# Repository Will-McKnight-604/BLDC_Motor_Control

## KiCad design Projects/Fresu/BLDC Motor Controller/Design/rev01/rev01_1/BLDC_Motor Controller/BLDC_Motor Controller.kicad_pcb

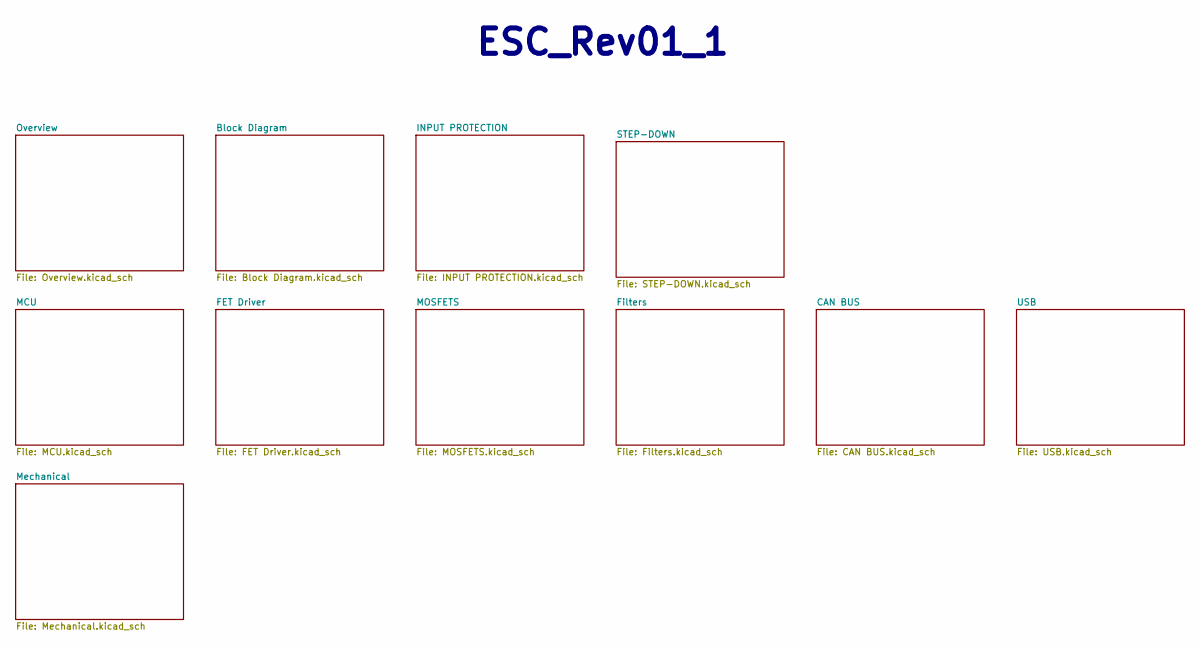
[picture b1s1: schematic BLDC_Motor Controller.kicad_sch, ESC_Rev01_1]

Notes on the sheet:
${TITLE}

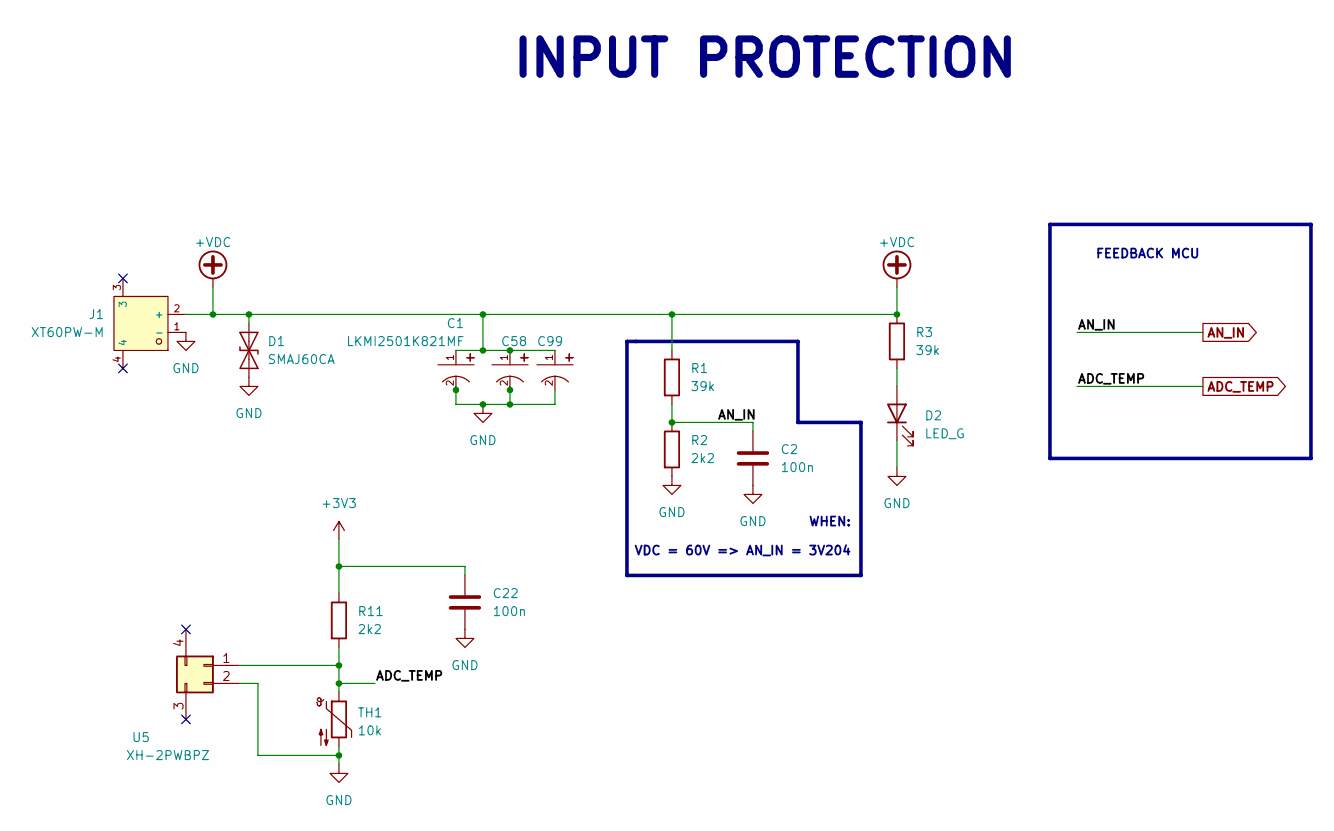
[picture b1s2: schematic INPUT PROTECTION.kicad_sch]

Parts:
C1, C58, C99: LKMI2501K821MF; CAP-TH_BD18.0-P7.50-D1.2-SIDE; LCSC C443097
C2, C22: 100n; C_0603_1608Metric
D1: SMAJ60CA; D_SMA
D2: LED_G; LED_1206_3216Metric
J1: XT60PW-M; CONN-TH_XT60PW-M; LCSC C98732
R1, R3: 39k; R_0603_1608Metric_Pad0.98x0.95mm_HandSolder
R2, R11: 2k2; R_0603_1608Metric_Pad0.98x0.95mm_HandSolder
TH1: 10k; R_0603_1608Metric_Pad0.98x0.95mm_HandSolder
U5: XH-2PWBPZ; CONN-SMD_XH-2PWBPZ

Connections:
+3V3: C22.1, R11.1; also elsewhere on the board
+VDC: C1.1, C58.1, C99.1, D1.2 (A2), J1.2 (+), R1.1, R3.1; also elsewhere on the board
ADC_TEMP: R11.2, TH1.1, U5.1; also elsewhere on the board
AN_IN: C2.1, R1.2, R2.1; also elsewhere on the board
GND: C1.2, C2.2, C22.2, C58.2, C99.2, D1.1 (A1), D2.1 (K), J1.1 (-), R2.2, TH1.2, U5.2; also elsewhere on the board
unnamed: D2.2 (A), R3.2

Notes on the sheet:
INPUT PROTECTION
FEEDBACK MCU
WHEN: VDC = 60V => AN_IN = 3V204

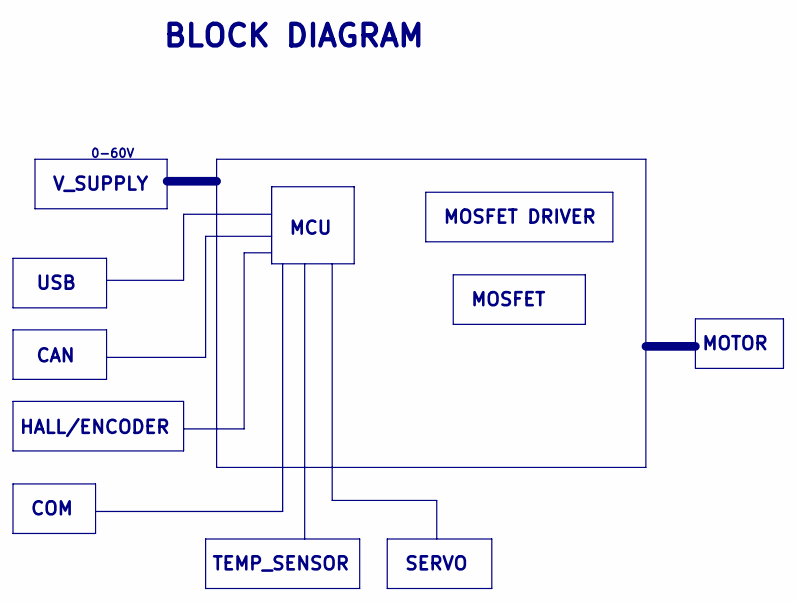
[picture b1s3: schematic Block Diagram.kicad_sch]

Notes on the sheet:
MCU
MOSFET
V_SUPPLY
MOTOR
TEMP_SENSOR
BLOCK DIAGRAM
USB
HALL/ENCODER
SERVO
COM
0-60V
MOSFET DRIVER
CAN

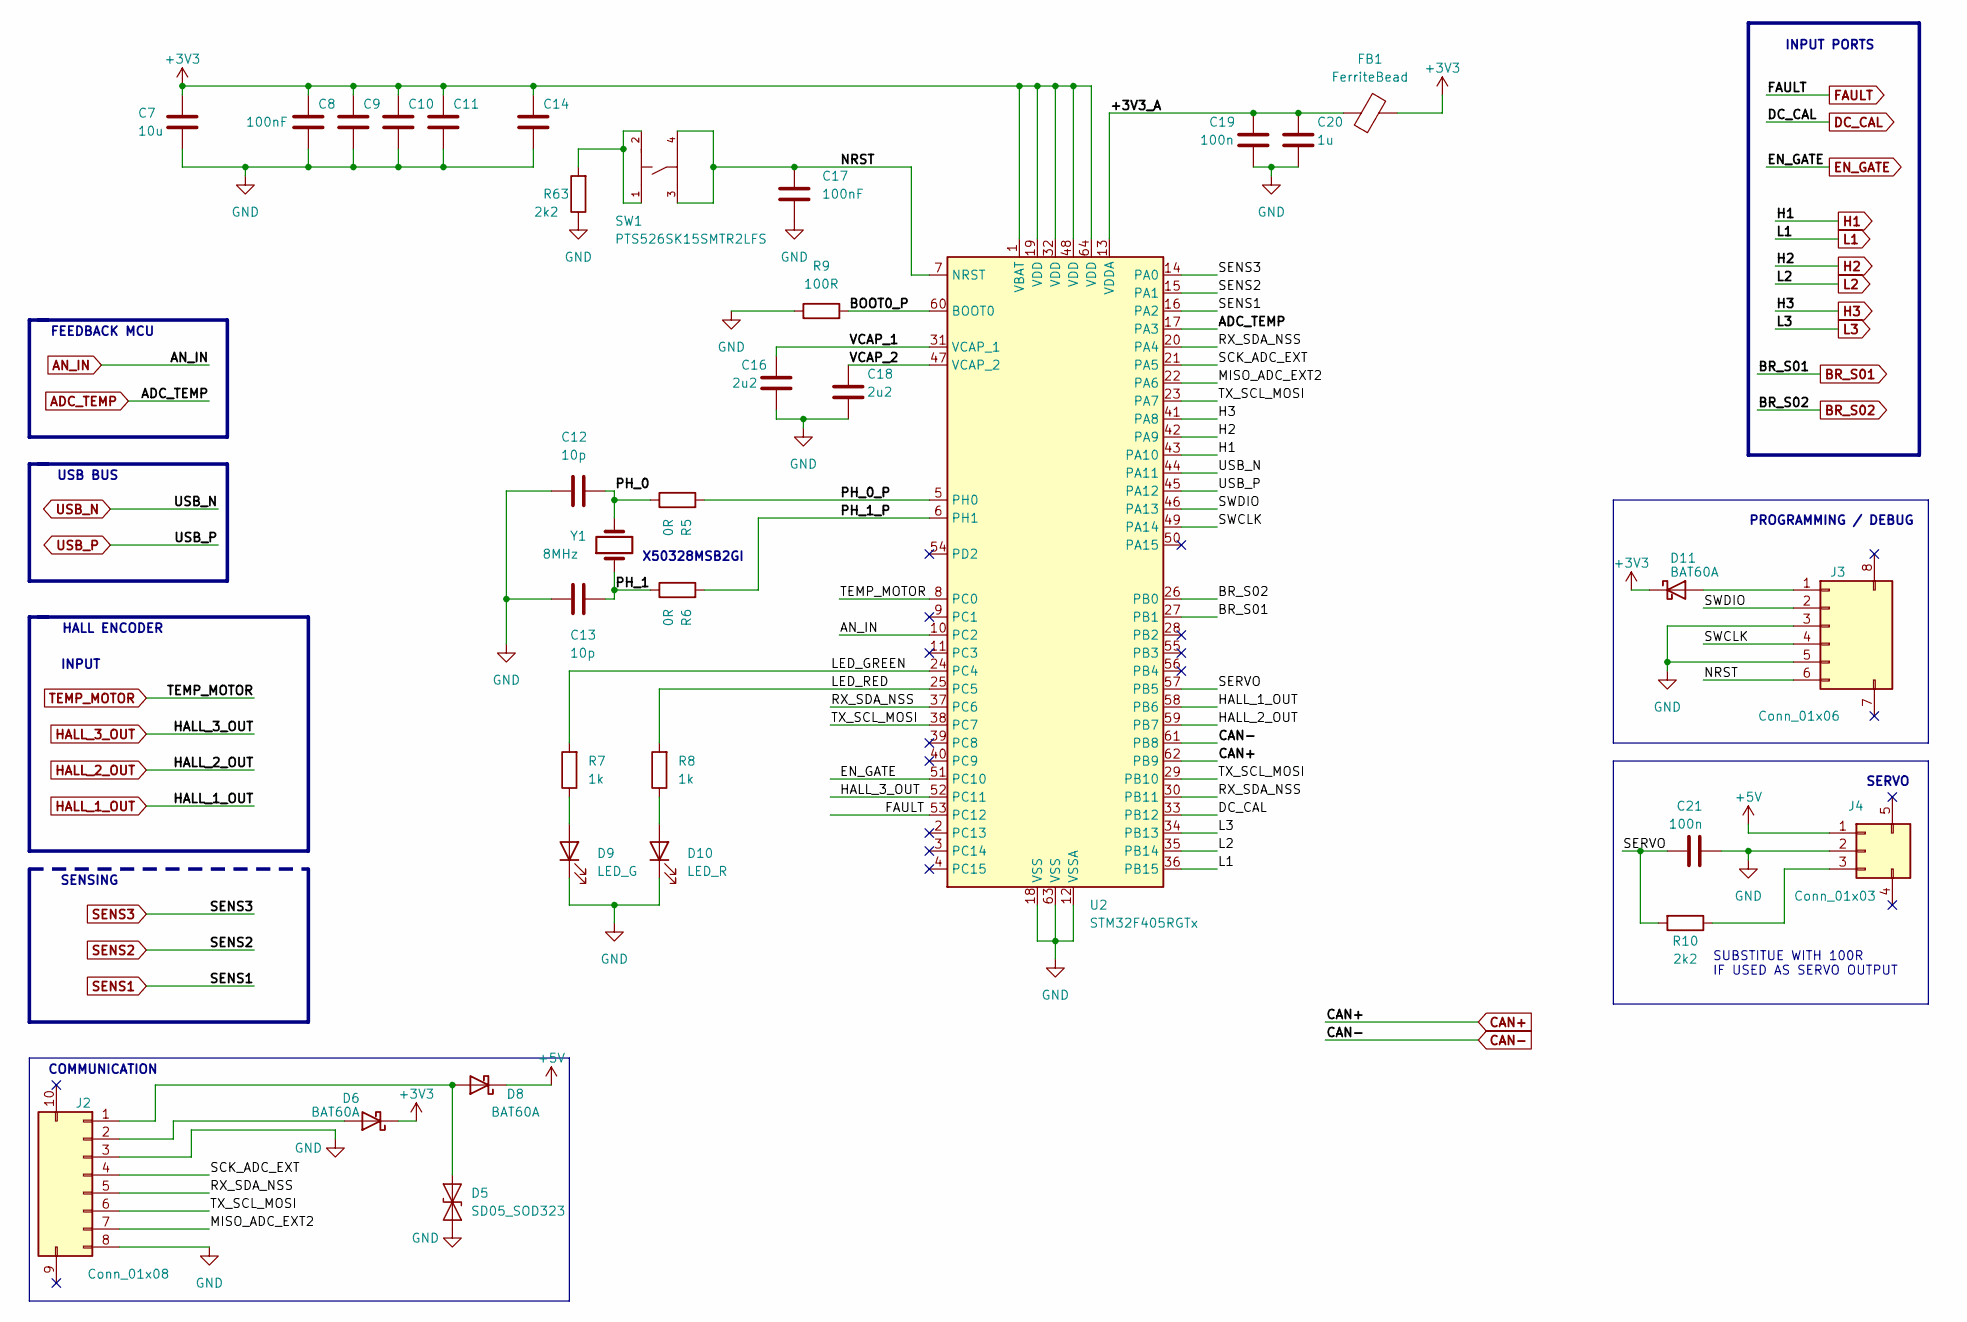
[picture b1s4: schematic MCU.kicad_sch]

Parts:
C7: 10u; C_0603_1608Metric
C8, C9, C10, C11, C14, C17: 100nF; C_0603_1608Metric
C12, C13: 10p; C_0603_1608Metric
C16, C18: 2u2; C_0603_1608Metric
C19, C21: 100n; C_0603_1608Metric
C20: 1u; C_0603_1608Metric
D5: SD05_SOD323; D_SOD-323
D6, D8, D11: BAT60A; D_SOD-323
D9: LED_G; LED_1206_3216Metric
D10: LED_R; LED_1206_3216Metric
FB1: FerriteBead; L_0603_1608Metric_Pad1.05x0.95mm_HandSolder
J2: Conn_01x08; CONN-SMD_8P-P2.50_HX25003-8AWB
J3: Conn_01x06; CONN-SMD_S6B-XH-SM4-TB-LF-SN
J4: Conn_01x03; CONN-SMD_XH-3AWB
R5, R6: 0R; R_0603_1608Metric_Pad0.98x0.95mm_HandSolder
R7, R8: 1k; R_0603_1608Metric_Pad0.98x0.95mm_HandSolder
R9: 100R; R_0603_1608Metric_Pad0.98x0.95mm_HandSolder
R10, R63: 2k2; R_0603_1608Metric_Pad0.98x0.95mm_HandSolder
SW1: PTS526SK15SMTR2LFS; SW-SMD_4P-L5.2-W5.2-P3.70-LS6.4; LCSC C2689521
U2: STM32F405RGTx; LQFP-64_10x10mm_P0.5mm
Y1: 8MHz; CRYSTAL-SMD_L5.0-W3.2

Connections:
+3V3: C7.1, C8.1, C9.1, C10.1, C11.1, C14.1, D6.1 (K), D11.1 (K), FB1.2, U2.1 (VBAT), U2.19 (VDD), U2.32 (VDD), U2.48 (VDD), U2.64 (VDD); also elsewhere on the board
+5V: D8.1 (K), J4.1; also elsewhere on the board
/MCU/+3V3_A: C19.1, C20.1, FB1.1, U2.13 (VDDA)
/MCU/BOOT0_P: R9.2, U2.60 (BOOT0)
/MCU/LED_GREEN: R7.2, U2.24 (PC4)
/MCU/LED_RED: R8.2, U2.25 (PC5)
/MCU/MISO_ADC_EXT2: J2.7, U2.22 (PA6)
/MCU/NRST: C17.1, J3.6, SW1.3, SW1.4, U2.7 (NRST)
/MCU/PH_0: C12.1, R5.1, Y1.2
/MCU/PH_0_P: R5.2, U2.5 (PH0)
/MCU/PH_1: C13.1, R6.1, Y1.1
/MCU/PH_1_P: R6.2, U2.6 (PH1)
/MCU/RX_SDA_NSS: J2.5, U2.20 (PA4), U2.30 (PB11), U2.37 (PC6)
/MCU/SCK_ADC_EXT: J2.4, U2.21 (PA5)
/MCU/SERVO: C21.1, R10.2, U2.57 (PB5)
/MCU/SWCLK: J3.4, U2.49 (PA14)
/MCU/SWDIO: J3.2, U2.46 (PA13)
/MCU/TX_SCL_MOSI: J2.6, U2.23 (PA7), U2.29 (PB10), U2.38 (PC7)
/MCU/VCAP_1: C16.1, U2.31 (VCAP_1)
/MCU/VCAP_2: C18.1, U2.47 (VCAP_2)
ADC_TEMP: U2.17 (PA3); also elsewhere on the board
AN_IN: U2.10 (PC2); also elsewhere on the board
BR_S01: U2.27 (PB1); also elsewhere on the board
BR_S02: U2.26 (PB0); also elsewhere on the board
CAN+: U2.62 (PB9); also elsewhere on the board
CAN-: U2.61 (PB8); also elsewhere on the board
DC_CAL: U2.33 (PB12); also elsewhere on the board
EN_GATE: U2.51 (PC10); also elsewhere on the board
FAULT: U2.53 (PC12); also elsewhere on the board
GND: C7.2, C8.2, C9.2, C10.2, C11.2, C12.2, C13.2, C14.2, C16.2, C17.2, C18.2, C19.2, C20.2, C21.2, D5.1 (A1), D9.1 (K), D10.1 (K), J2.3, J2.8, J3.3, J3.5, J4.2, R9.1, R63.1, U2.12 (VSSA), U2.18 (VSS), U2.63 (VSS); also elsewhere on the board
H1: U2.43 (PA10); also elsewhere on the board
H2: U2.42 (PA9); also elsewhere on the board
H3: U2.41 (PA8); also elsewhere on the board
HALL_1_OUT: U2.58 (PB6); also elsewhere on the board
HALL_2_OUT: U2.59 (PB7); also elsewhere on the board
HALL_3_OUT: U2.52 (PC11); also elsewhere on the board
L1: U2.36 (PB15); also elsewhere on the board
L2: U2.35 (PB14); also elsewhere on the board
L3: U2.34 (PB13); also elsewhere on the board
unnamed: D5.2 (A2), D8.2 (A), J2.1
unnamed: D6.2 (A), J2.2
unnamed: D9.2 (A), R7.1
unnamed: D10.2 (A), R8.1
unnamed: D11.2 (A), J3.1
unnamed: J4.3, R10.1
unnamed: R63.2, SW1.1, SW1.2
SENS1: U2.16 (PA2); also elsewhere on the board
SENS2: U2.15 (PA1); also elsewhere on the board
SENS3: U2.14 (PA0); also elsewhere on the board
TEMP_MOTOR: U2.8 (PC0); also elsewhere on the board
USB_N: U2.44 (PA11); also elsewhere on the board
USB_P: U2.45 (PA12); also elsewhere on the board

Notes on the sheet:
SERVO
INPUT PORTS
USB BUS
HALL ENCODER
X50328MSB2GI
INPUT
COMMUNICATION
FEEDBACK MCU
SUBSTITUE WITH 100R IF USED AS SERVO OUTPUT
SENSING
PROGRAMMING / DEBUG

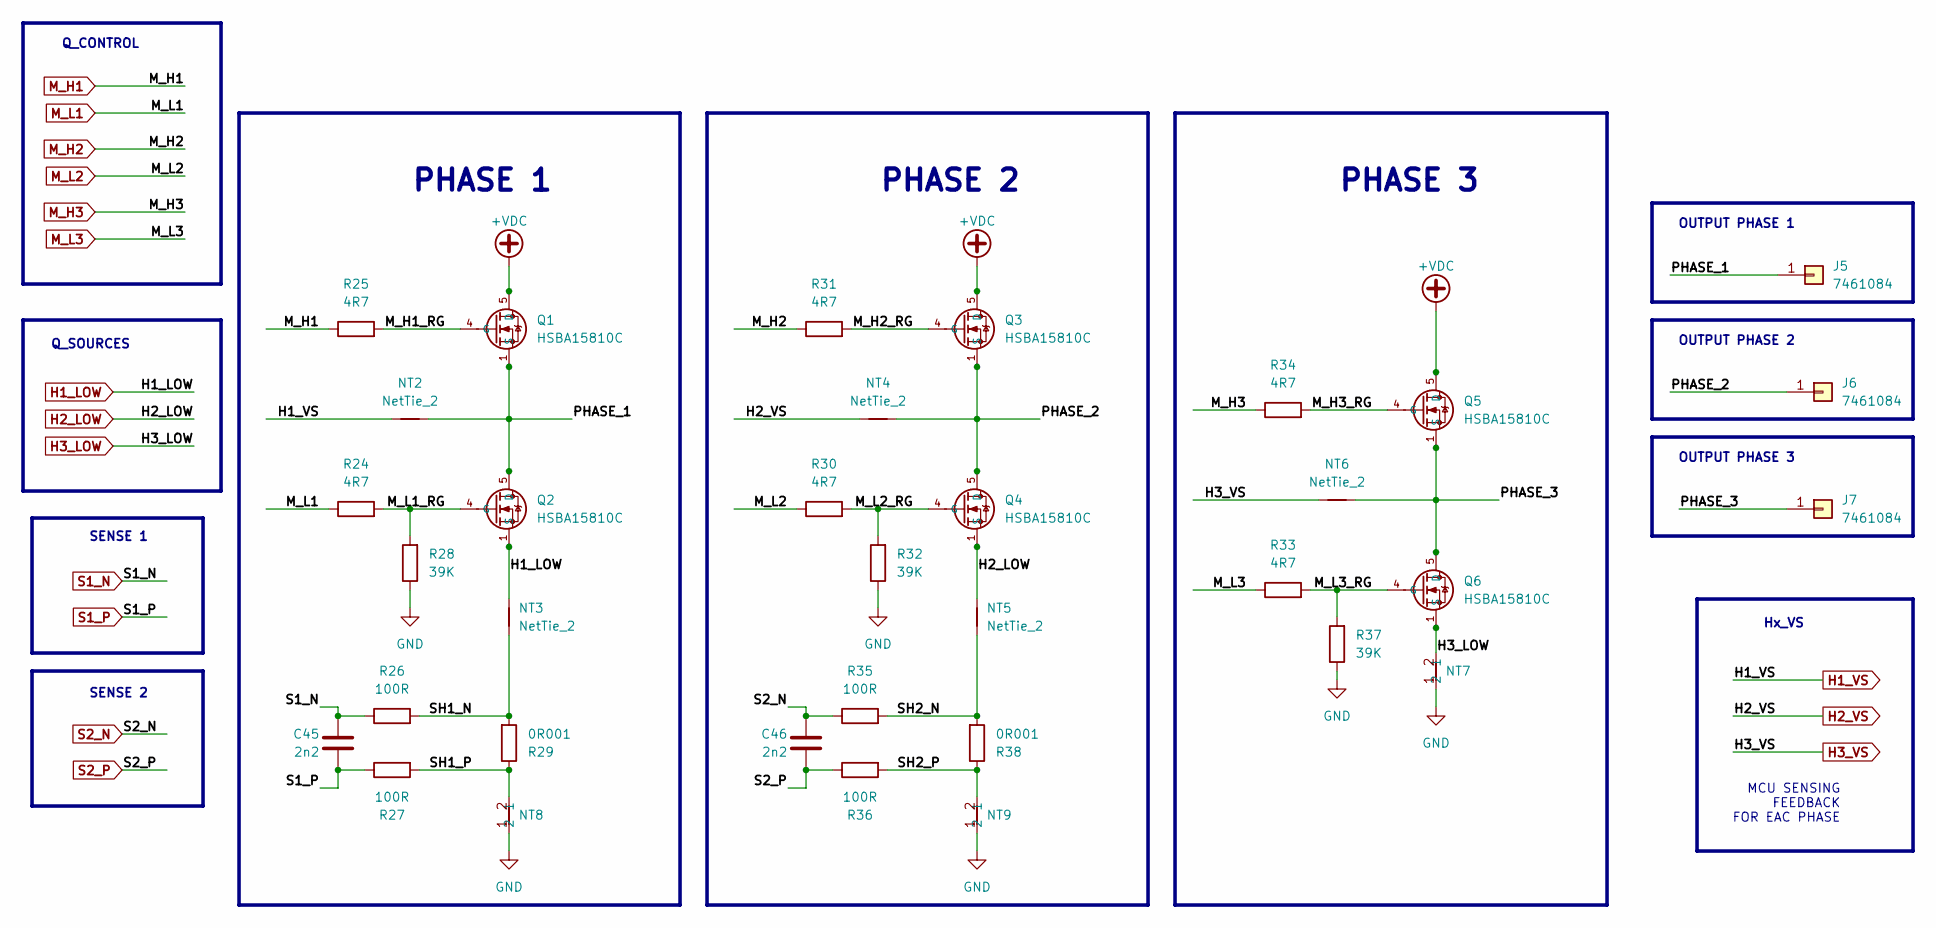
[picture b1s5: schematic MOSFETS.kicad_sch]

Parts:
C45, C46: 2n2; C_0603_1608Metric
J5, J6, J7: 7461084; WE_7461084
NT2, NT4, NT6: NetTie_2; NetTie-2_SMD_Pad0.5mm
NT3, NT5: NetTie_2; NetTie_SMD_Pad_3.00mm
NT7, NT8, NT9: Net_Tie_PWR; NetTie_SMD_Pad_6.00mm
Q1, Q2, Q3, Q4, Q5, Q6: HSBA15810C; PQFN-8_L6.0-W5.0-P1.27-LS6.0-BL; LCSC C845605
R24, R25, R30, R31, R33, R34: 4R7; R_0603_1608Metric_Pad0.98x0.95mm_HandSolder
R26, R27, R35, R36: 100R; R_0603_1608Metric_Pad0.98x0.95mm_HandSolder
R28, R32, R37: 39K; R_0603_1608Metric_Pad0.98x0.95mm_HandSolder
R29, R38: 0R001; RES-SMD_L7.0-W6.7

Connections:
+VDC: Q1.5 (D), Q1.6 (D), Q1.7 (D), Q1.8 (D), Q1.9 (D), Q3.5 (D), Q3.6 (D), Q3.7 (D), Q3.8 (D), Q3.9 (D), Q5.5 (D), Q5.6 (D), Q5.7 (D), Q5.8 (D), Q5.9 (D); also elsewhere on the board
/MOSFETS/M_H1_RG: Q1.4 (G), R25.2
/MOSFETS/M_H2_RG: Q3.4 (G), R31.2
/MOSFETS/M_H3_RG: Q5.4 (G), R34.2
/MOSFETS/M_L1_RG: Q2.4 (G), R24.2, R28.2
/MOSFETS/M_L2_RG: Q4.4 (G), R30.2, R32.2
/MOSFETS/M_L3_RG: Q6.4 (G), R33.2, R37.2
/MOSFETS/PHASE_1: J5.1, NT2.2, Q1.1 (S), Q1.2 (S), Q1.3 (S), Q2.5 (D), Q2.6 (D), Q2.7 (D), Q2.8 (D), Q2.9 (D)
/MOSFETS/PHASE_2: J6.1, NT4.2, Q3.1 (S), Q3.2 (S), Q3.3 (S), Q4.5 (D), Q4.6 (D), Q4.7 (D), Q4.8 (D), Q4.9 (D)
/MOSFETS/PHASE_3: J7.1, NT6.2, Q5.1 (S), Q5.2 (S), Q5.3 (S), Q6.5 (D), Q6.6 (D), Q6.7 (D), Q6.8 (D), Q6.9 (D)
/MOSFETS/SH1_N: NT3.1, R26.2, R29.2
/MOSFETS/SH1_P: NT8.2, R27.2, R29.1
/MOSFETS/SH2_N: NT5.1, R35.2, R38.2
/MOSFETS/SH2_P: NT9.2, R36.2, R38.1
GND: NT7.1, NT8.1, NT9.1, R28.1, R32.1, R37.1; also elsewhere on the board
H1_LOW: NT3.2, Q2.1 (S), Q2.2 (S), Q2.3 (S); also elsewhere on the board
H1_VS: NT2.1; also elsewhere on the board
H2_LOW: NT5.2, Q4.1 (S), Q4.2 (S), Q4.3 (S); also elsewhere on the board
H2_VS: NT4.1; also elsewhere on the board
H3_LOW: NT7.2, Q6.1 (S), Q6.2 (S), Q6.3 (S); also elsewhere on the board
H3_VS: NT6.1; also elsewhere on the board
M_H1: R25.1; also elsewhere on the board
M_H2: R31.1; also elsewhere on the board
M_H3: R34.1; also elsewhere on the board
M_L1: R24.1; also elsewhere on the board
M_L2: R30.1; also elsewhere on the board
M_L3: R33.1; also elsewhere on the board
S1_N: C45.1, R26.1; also elsewhere on the board
S1_P: C45.2, R27.1; also elsewhere on the board
S2_N: C46.1, R35.1; also elsewhere on the board
S2_P: C46.2, R36.1; also elsewhere on the board

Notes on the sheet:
OUTPUT PHASE 1
Q_SOURCES
PHASE 1
PHASE 2
OUTPUT PHASE 3
Hx_VS
SENSE 1
Q_CONTROL
SENSE 2
OUTPUT PHASE 2
MCU SENSING FEEDBACK FOR EAC PHASE
PHASE 3

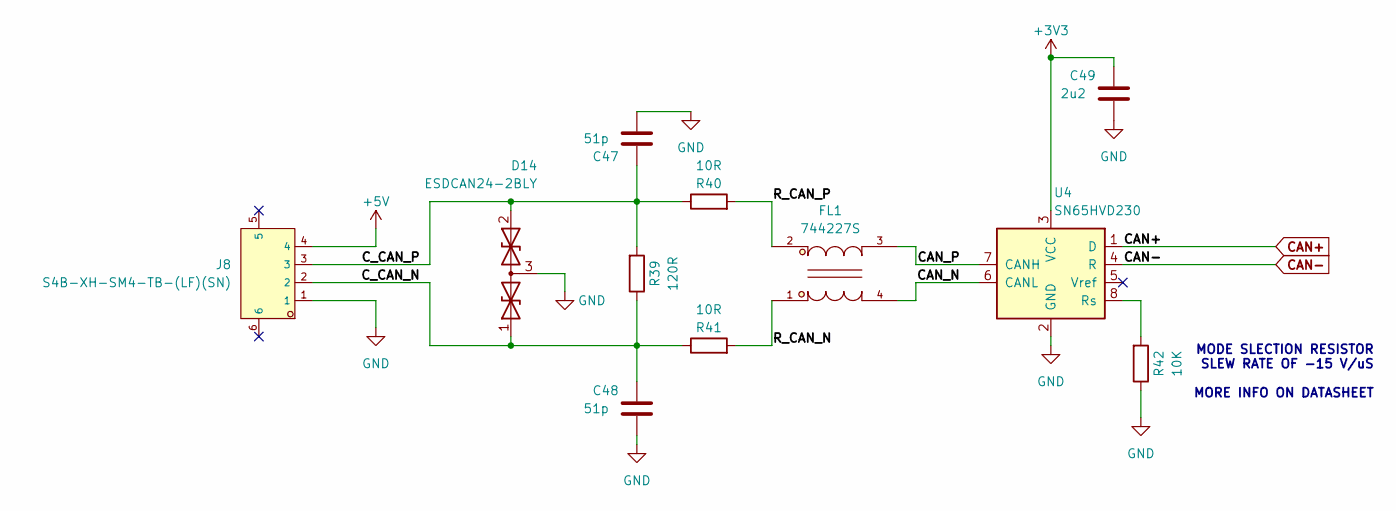
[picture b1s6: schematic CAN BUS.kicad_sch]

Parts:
C47, C48: 51p; C_0603_1608Metric
C49: 2u2; C_0603_1608Metric
D14: ESDCAN24-2BLY; TSOT-23
FL1: 744227S; FILTER-SMD_4P-L9.2-W6.0-P2.54-TL; LCSC C2651119
J8: S4B-XH-SM4-TB-(LF)(SN); CONN-SMD_S4B-XH-SM4-TB-LF-SN; LCSC C161861
R39: 120R; R_0603_1608Metric_Pad0.98x0.95mm_HandSolder
R40, R41: 10R; R_0603_1608Metric_Pad0.98x0.95mm_HandSolder
R42: 10K; R_0603_1608Metric_Pad0.98x0.95mm_HandSolder
U4: SN65HVD230; SOIC-8_3.9x4.9mm_P1.27mm

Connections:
+3V3: C49.1, U4.3 (VCC); also elsewhere on the board
+5V: J8.4; also elsewhere on the board
/CAN BUS/CAN_N: FL1.4, U4.6 (CANL)
/CAN BUS/CAN_P: FL1.3, U4.7 (CANH)
/CAN BUS/C_CAN_N: C48.1, D14.1 (A1), J8.2, R39.1, R41.1
/CAN BUS/C_CAN_P: C47.1, D14.2 (A2), J8.3, R39.2, R40.1
/CAN BUS/R_CAN_N: FL1.1, R41.2
/CAN BUS/R_CAN_P: FL1.2, R40.2
CAN+: U4.1 (D); also elsewhere on the board
CAN-: U4.4 (R); also elsewhere on the board
GND: C47.2, C48.2, C49.2, D14.3 (common), J8.1, R42.1, U4.2 (GND); also elsewhere on the board
unnamed: R42.2, U4.8 (Rs)

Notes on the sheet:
MODE SLECTION RESISTOR SLEW RATE OF -15 V/uS MORE INFO ON DATASHEET

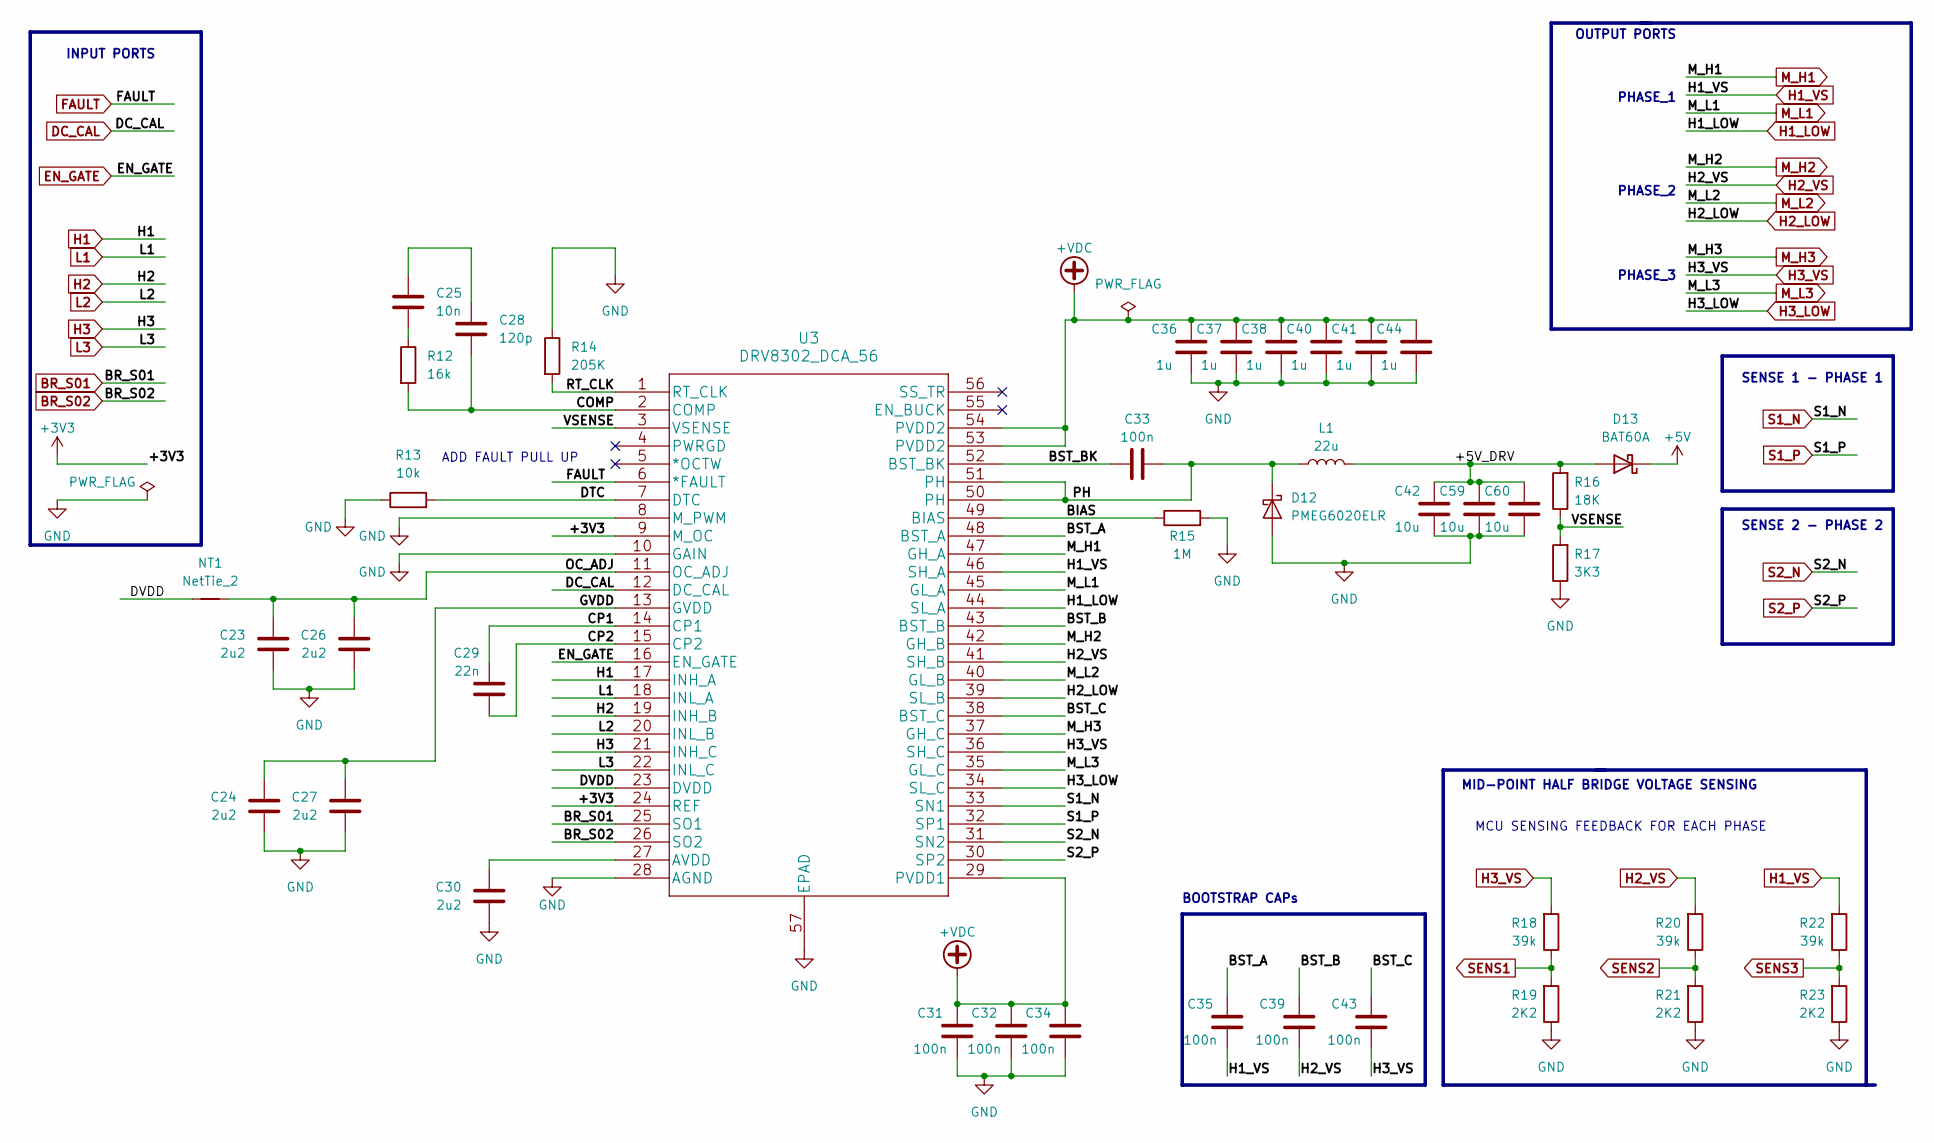
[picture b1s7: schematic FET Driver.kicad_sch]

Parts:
C23, C24, C26, C27, C30: 2u2; C_0603_1608Metric
C25: 10n; C_0603_1608Metric
C28: 120p; C_0603_1608Metric
C29: 22n; C_0603_1608Metric
C31, C32, C33, C34, C35, C39, C43: 100n; C_0603_1608Metric
C36, C37, C38, C40, C41, C44: 1u; C_0603_1608Metric
C42, C59, C60: 10u; C_1206_3216Metric
D12: PMEG6020ELR; Nexperia_CFP3_SOD-123W
D13: BAT60A; D_SOD-323
L1: 22u; IND-SMD_L7.8-W7.8_SDR0805
NT1: NetTie_2; NetTie_SMD_Pad_0.2mm
R12: 16k; R_0603_1608Metric_Pad0.98x0.95mm_HandSolder
R13: 10k; R_0603_1608Metric_Pad0.98x0.95mm_HandSolder
R14: 205K; R_0603_1608Metric_Pad0.98x0.95mm_HandSolder
R15: 1M; R_0603_1608Metric_Pad0.98x0.95mm_HandSolder
R16: 18K; R_0603_1608Metric_Pad0.98x0.95mm_HandSolder
R17: 3K3; R_0603_1608Metric_Pad0.98x0.95mm_HandSolder
R18, R20, R22: 39k; R_0603_1608Metric_Pad0.98x0.95mm_HandSolder
R19, R21, R23: 2K2; R_0603_1608Metric_Pad0.98x0.95mm_HandSolder
U3: DRV8302_DCA_56; HTSSOP-56-1EP_6.1x14mm_P0.5mm_EP3.61x6.35mm

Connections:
+3V3: U3.9 (M_OC), U3.24 (REF); also elsewhere on the board
+5V: D13.1 (K); also elsewhere on the board
+VDC: C31.2, C32.2, C34.2, C36.2, C37.2, C38.2, C40.2, C41.2, C44.2, U3.29 (PVDD1), U3.53 (PVDD2), U3.54 (PVDD2); also elsewhere on the board
/FET Driver/+5V_DRV: C42.2, C59.2, C60.2, D13.2 (A), L1.2, R16.2
/FET Driver/BIAS: R15.1, U3.49 (BIAS)
/FET Driver/BST_A: C35.2, U3.48 (BST_A)
/FET Driver/BST_B: C39.2, U3.43 (BST_B)
/FET Driver/BST_BK: C33.1, U3.52 (BST_BK)
/FET Driver/BST_C: C43.2, U3.38 (BST_C)
/FET Driver/COMP: C28.2, R12.2, U3.2 (COMP)
/FET Driver/CP1: C29.2, U3.14 (CP1)
/FET Driver/CP2: C29.1, U3.15 (CP2)
/FET Driver/DTC: R13.2, U3.7 (DTC)
/FET Driver/DVDD: NT1.1, U3.23 (DVDD)
/FET Driver/GVDD: C24.2, C27.2, U3.13 (GVDD)
/FET Driver/OC_ADJ: C23.2, C26.2, NT1.2, U3.11 (OC_ADJ)
/FET Driver/PH: C33.2, D12.1 (K), L1.1, U3.50 (PH), U3.51 (PH)
/FET Driver/RT_CLK: R14.2, U3.1 (RT_CLK)
/FET Driver/VSENSE: R16.1, R17.2, U3.3 (VSENSE)
BR_S01: U3.25 (SO1); also elsewhere on the board
BR_S02: U3.26 (SO2); also elsewhere on the board
DC_CAL: U3.12 (DC_CAL); also elsewhere on the board
EN_GATE: U3.16 (EN_GATE); also elsewhere on the board
FAULT: U3.6 (*FAULT); also elsewhere on the board
GND: C23.1, C24.1, C26.1, C27.1, C30.1, C31.1, C32.1, C34.1, C36.1, C37.1, C38.1, C40.1, C41.1, C42.1, C44.1, C59.1, C60.1, D12.2 (A), R13.1, R14.1, R15.2, R17.1, R19.1, R21.1, R23.1, U3.8 (M_PWM), U3.10 (GAIN), U3.28 (AGND), U3.57 (EPAD); also elsewhere on the board
H1: U3.17 (INH_A); also elsewhere on the board
H1_LOW: U3.44 (SL_A); also elsewhere on the board
H1_VS: C35.1, R22.2, U3.46 (SH_A); also elsewhere on the board
H2: U3.19 (INH_B); also elsewhere on the board
H2_LOW: U3.39 (SL_B); also elsewhere on the board
H2_VS: C39.1, R20.2, U3.41 (SH_B); also elsewhere on the board
H3: U3.21 (INH_C); also elsewhere on the board
H3_LOW: U3.34 (SL_C); also elsewhere on the board
H3_VS: C43.1, R18.2, U3.36 (SH_C); also elsewhere on the board
L1: U3.18 (INL_A); also elsewhere on the board
L2: U3.20 (INL_B); also elsewhere on the board
L3: U3.22 (INL_C); also elsewhere on the board
M_H1: U3.47 (GH_A); also elsewhere on the board
M_H2: U3.42 (GH_B); also elsewhere on the board
M_H3: U3.37 (GH_C); also elsewhere on the board
M_L1: U3.45 (GL_A); also elsewhere on the board
M_L2: U3.40 (GL_B); also elsewhere on the board
M_L3: U3.35 (GL_C); also elsewhere on the board
unnamed: C25.1, C28.1
unnamed: C25.2, R12.1
unnamed: C30.2, U3.27 (AVDD)
S1_N: U3.33 (SN1); also elsewhere on the board
S1_P: U3.32 (SP1); also elsewhere on the board
S2_N: U3.31 (SN2); also elsewhere on the board
S2_P: U3.30 (SP2); also elsewhere on the board
SENS1: R18.1, R19.2; also elsewhere on the board
SENS2: R20.1, R21.2; also elsewhere on the board
SENS3: R22.1, R23.2; also elsewhere on the board

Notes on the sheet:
PHASE_2
BOOTSTRAP CAPs
INPUT PORTS
OUTPUT PORTS
MID-POINT HALF BRIDGE VOLTAGE SENSING
MCU SENSING FEEDBACK FOR EACH PHASE
PHASE_3
PHASE_1
SENSE 2 - PHASE 2
ADD FAULT PULL UP
SENSE 1 - PHASE 1

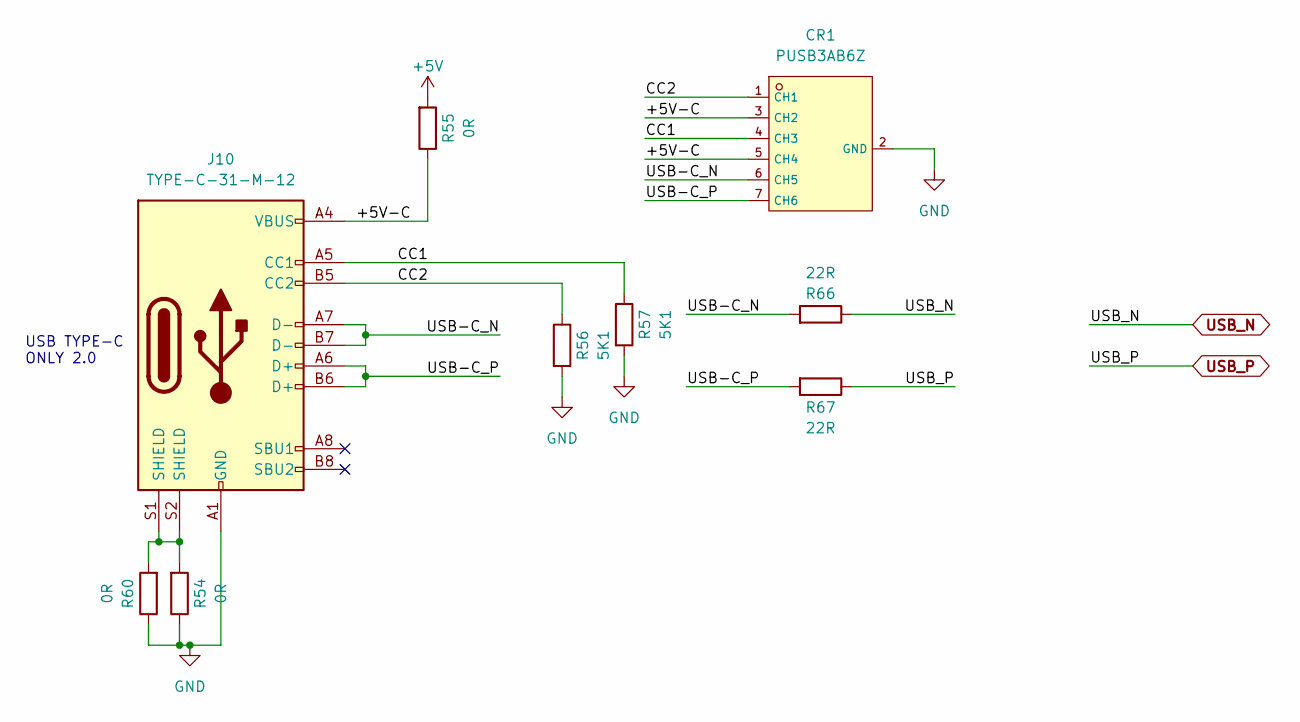
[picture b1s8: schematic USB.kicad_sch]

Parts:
CR1: PUSB3AB6Z; XSON-7_L2.2-W1.2-P0.50-BL; LCSC C553550
J10: TYPE-C-31-M-12; USB-C_SMD-TYPE-C-31-M-12
R54, R55, R60: 0R; R_0603_1608Metric_Pad0.98x0.95mm_HandSolder
R56, R57: 5K1; R_0603_1608Metric_Pad0.98x0.95mm_HandSolder
R66, R67: 22R; R_0603_1608Metric_Pad0.98x0.95mm_HandSolder

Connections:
+5V: R55.2; also elsewhere on the board
/USB/+5V-C: CR1.3 (CH2), CR1.5 (CH4), J10.A4 (VBUS), J10.A9 (VBUS), J10.B4 (VBUS), J10.B9 (VBUS), R55.1
/USB/CC1: CR1.4 (CH3), J10.A5 (CC1), R57.1
/USB/CC2: CR1.1 (CH1), J10.B5 (CC2), R56.1
/USB/USB-C_N: CR1.6 (CH5), J10.A7 (D-), J10.B7 (D-), R66.2
/USB/USB-C_P: CR1.7 (CH6), J10.A6 (D+), J10.B6 (D+), R67.2
GND: CR1.2 (GND), J10.A1 (GND), J10.A12 (GND), J10.B1 (GND), J10.B12 (GND), R54.1, R56.2, R57.2, R60.1; also elsewhere on the board
unnamed: J10.S1 (SHIELD), J10.S2 (SHIELD), R54.2, R60.2
USB_N: R66.1; also elsewhere on the board
USB_P: R67.1; also elsewhere on the board

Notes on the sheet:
USB TYPE-C ONLY 2.0

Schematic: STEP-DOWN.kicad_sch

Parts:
C3, C4, C5, C6: 1u; C_0603_1608Metric
D3: BAT60A; D_SOD-323
D4, D15: LED_G; LED_1206_3216Metric
R4, R62: 1k; R_0603_1608Metric_Pad0.98x0.95mm_HandSolder
U1: AMS1117-3.3; SOT-223-3_TabPin2

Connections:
+3V3: D3.1 (K), R4.1; also elsewhere on the board
+5V: C3.1, C4.1, R62.1, U1.3 (VI); also elsewhere on the board
/STEP-DOWN/+3v3Vout: C5.1, C6.1, D3.2 (A), U1.2 (VO)
GND: C3.2, C4.2, C5.2, C6.2, D4.1 (K), D15.1 (K), U1.1 (GND); also elsewhere on the board
unnamed: D4.2 (A), R4.2
unnamed: D15.2 (A), R62.2

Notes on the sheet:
STEP DOWN

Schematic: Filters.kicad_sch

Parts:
C50, C51, C52, C53: 4n7; C_0603_1608Metric
C54, C55, C56, C57: 100n; C_0603_1608Metric
J9: Conn_01x06; CONN-SMD_S6B-XH-SM4-TB-LF-SN
R43, R44, R45: 2k2; R_0603_1608Metric_Pad0.98x0.95mm_HandSolder
R46, R47, R48, R49: 10k; R_0603_1608Metric_Pad0.98x0.95mm_HandSolder
R61: 0R; R_0603_1608Metric_Pad0.98x0.95mm_HandSolder

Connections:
+3V3: C54.1, C55.1, C56.1, C57.1, R43.1, R44.1, R45.1, R46.1; also elsewhere on the board
+5V: J9.6; also elsewhere on the board
/Filters/HALL_1_IN: C50.1, J9.4, R43.2, R47.1
/Filters/HALL_2_IN: C51.1, J9.3, R44.2, R48.1
/Filters/HALL_3_IN: C52.1, J9.2, R45.2, R49.1
/Filters/TEMP_IN: C53.1, J9.5, R46.2, R61.1
GND: C50.2, C51.2, C52.2, C53.2, C54.2, C55.2, C56.2, C57.2, J9.1; also elsewhere on the board
HALL_1_OUT: R47.2; also elsewhere on the board
HALL_2_OUT: R48.2; also elsewhere on the board
HALL_3_OUT: R49.2; also elsewhere on the board
TEMP_MOTOR: R61.2; also elsewhere on the board

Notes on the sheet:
TEMP_MOTOR FILTER
OUTPUT
HALL_3 FILTER
HALL ENCODER TO MCU =>
HALL_2 FILTER
HALL_1 FILTER

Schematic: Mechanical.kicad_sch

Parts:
H1, H2, H3, H4: MountingHole_Pad; MountingHole_3.2mm_M3_Pad_Via
R50, R51, R52, R53: 0R; R_0603_1608Metric_Pad0.98x0.95mm_HandSolder

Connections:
GND: R50.1, R51.1, R52.1, R53.1; also elsewhere on the board
unnamed: H1.1, R51.2
unnamed: H2.1, R50.2
unnamed: H3.1, R52.2
unnamed: H4.1, R53.2
